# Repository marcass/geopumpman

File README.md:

# geopumpman
Manage climate in home using a geothermal heatpump, solvers, predictive weather models and PID control

## Components

### Software

* Predictor of thermal requirements
   * Weather data, eg https://pypi.org/project/weather-api/
* Observer of climate conditions, eg https://github.com/marcass/esp32-sensornet
   * Temperature sensors
      * In slab
      * In lower storey/upper storey
      * Outside
   * Lux sensors (light ingress)
* Controller of heating/cooling plant
   * PID control on heating/cooling demand
   * Solvers, eg https://github.com/Pyomo
   * Extended Kalman filter?
* Heating/cooling plant
   * Fail-safes
* UI (web?)

### Hardware
* Comission ground source heatpump
* containerise software for easier hardware transition 
* Standard brain running linux

# Links
* https://www.researchgate.net/publication/327136772_A_Python-Based_Toolbox_for_Model_Predictive_Control_Applied_to_Buildings
* https://filterpy.readthedocs.io/en/latest/kalman/ExtendedKalmanFilter.html

# Things to do
* Work out how to perist and share data between containers for influxdb

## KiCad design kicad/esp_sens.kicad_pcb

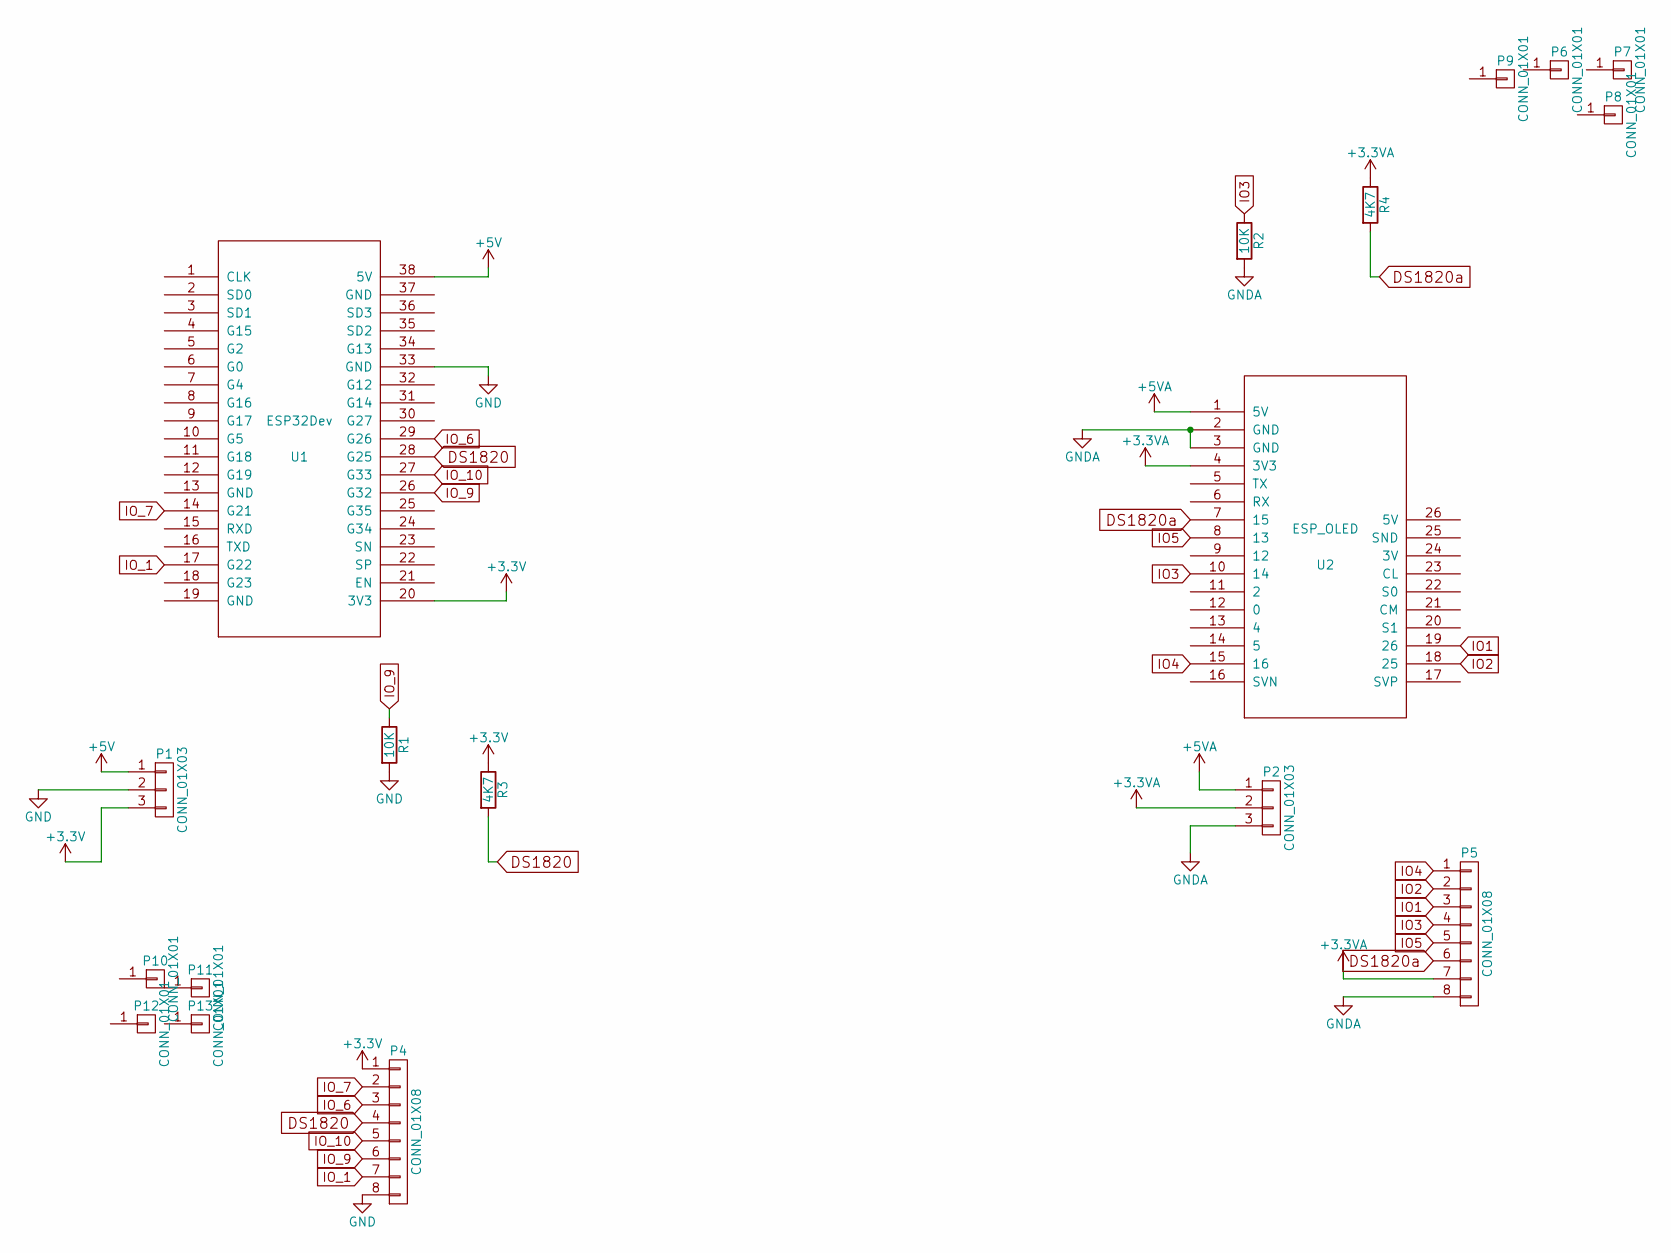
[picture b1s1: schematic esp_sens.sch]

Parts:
P1, P2: CONN_01X03; PhoenixContact_MCV_1,5_3-G-3.81_1x03_P3.81mm_Vertical
P4, P5: CONN_01X08; PhoenixContact_MCV_1,5_8-G-3.81_1x08_P3.81mm_Vertical
P6, P7, P8, P9, P10, P11, P12, P13: CONN_01X01; MountingHole_4.3mm_M4_DIN965_Pad
R1, R2: 10K; R_Axial_DIN0207_L6.3mm_D2.5mm_P10.16mm_Horizontal
R3, R4: 4K7; R_Axial_DIN0207_L6.3mm_D2.5mm_P10.16mm_Horizontal
U1: ESP32Dev; ESP32-DEV-WROOM
U2: ESP_OLED

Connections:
+3.3VA: P2.2, P5.7, R4.1, U2.4 (3V3)
+3V3: P1.3, P4.1, R3.1, U1.20 (3V3)
+5V: P1.1, U1.38 (5V)
+5VA: P2.1, U2.1 (5V)
DS1820: P4.4, R3.2, U1.28 (G25)
DS1820a: P5.6, R4.2, U2.7 (15)
GND: P1.2, P4.8, R1.2, U1.33 (GND)
GNDA: P2.3, P5.8, R2.2, U2.2 (GND), U2.3 (GND)
IO1: P5.3, U2.19 (26)
IO2: P5.2, U2.18 (25)
IO3: P5.4, R2.1, U2.10 (14)
IO4: P5.1, U2.15 (16)
IO5: P5.5, U2.8 (13)
IO_1: P4.7, U1.17 (G22)
IO_6: P4.3, U1.29 (G26)
IO_7: P4.2, U1.14 (G21)
IO_9: P4.6, R1.1, U1.26 (G32)
IO_10: P4.5, U1.27 (G33)

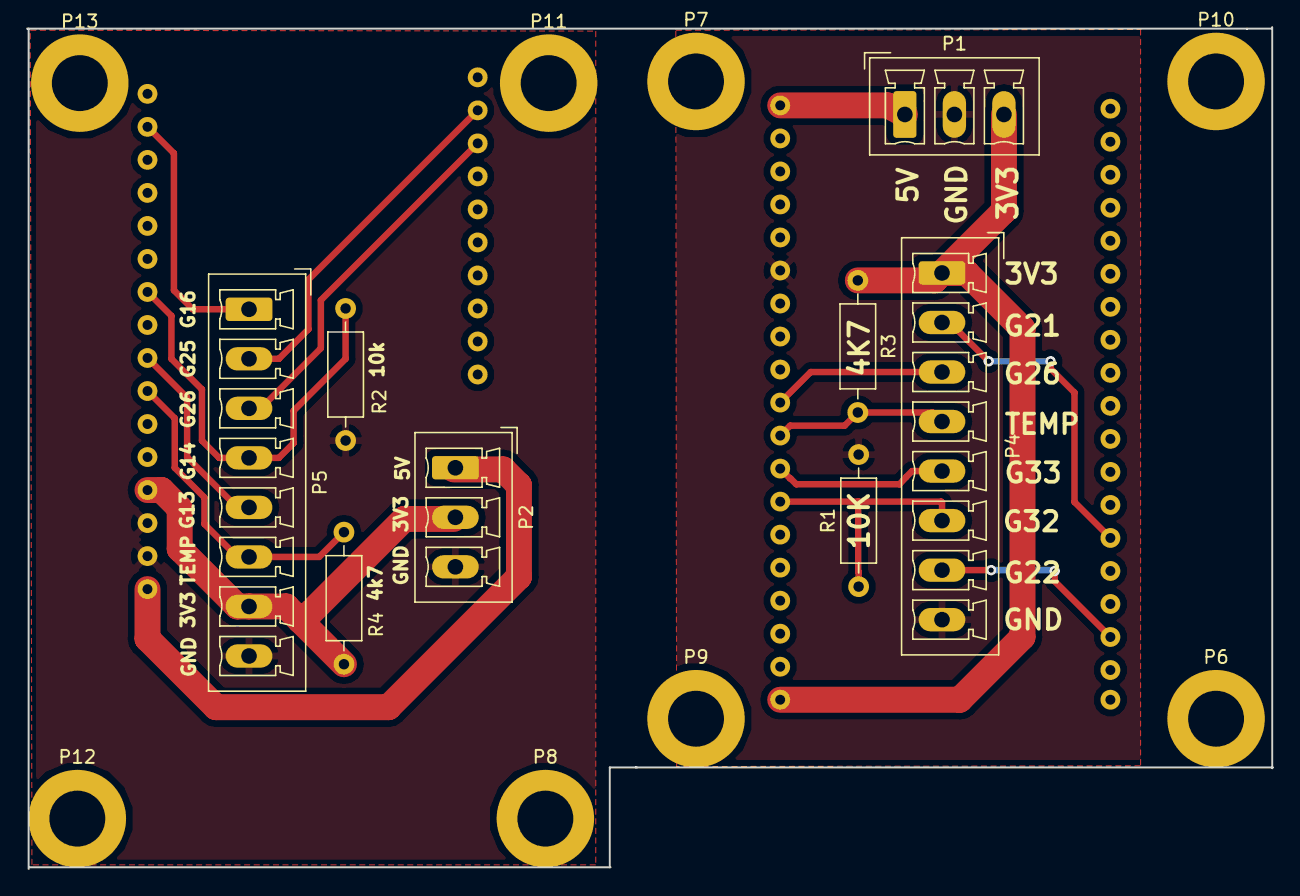
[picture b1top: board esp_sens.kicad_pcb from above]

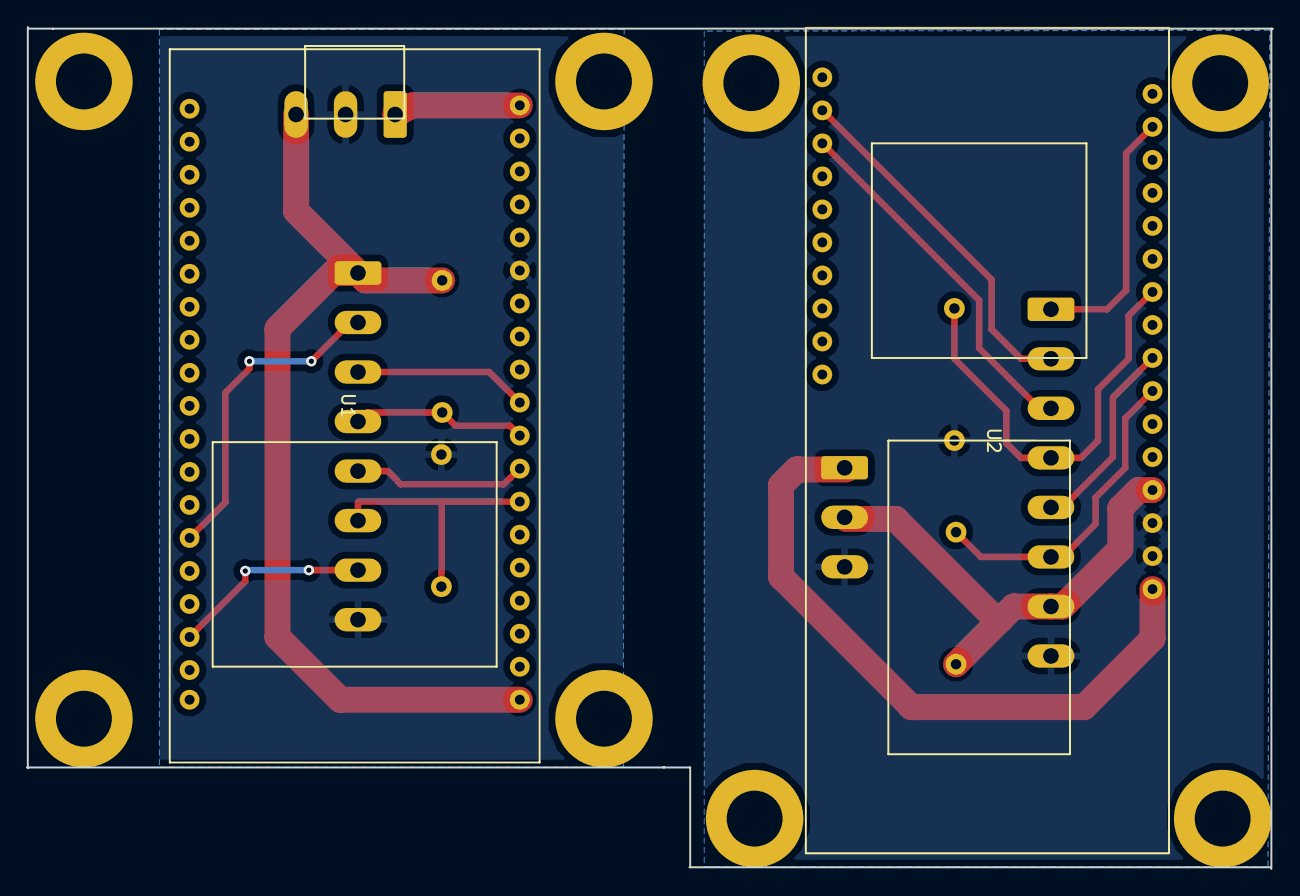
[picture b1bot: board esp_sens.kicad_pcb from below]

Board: 2 copper layers, 95.9 x 64.8 mm, 18 parts (2 on the bottom side), 18 nets.

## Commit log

2019-01-10 getting some structure and starting containerisation
2019-01-10 getting things arranged for testing sensors and peristent data in docker
2019-01-11 fiddling with weathe api
2019-01-14 using openweathermap
2019-01-15 can get sunny times
2019-04-12 started sensor platform
2019-04-12 2 boards in one
2019-04-12 pin reassignment...
2019-04-15 final board roundup
2019-04-15 label boards to do
2019-04-16 boards are labelled and plug size changed
2019-04-18 plotted boards
2019-10-09 started pcb for 1-wire connectors
2019-10-16 sketch for collecting temps
2019-10-16 added a serial listener
2019-10-16 timestamps...
2019-10-16 updated address
2019-10-17 sorting data
2019-10-17 working, just need to format timesstamp
2019-10-17 updated so datetime is now rendered as string
2019-10-17 sloed sampling rate
2019-10-17 added some data
2019-10-18 updated date separator
2019-10-18 adding plotting
2019-10-22 real world data
2019-11-03 started footprint for connector
2019-11-05 finsished model for rj45 connector
2019-11-06 soreted footprints
2019-11-06 started board
2019-11-07 added schottky diode
2019-11-08 laying out pcb
2019-11-15 finished pcd
2019-11-15 finished schematic
2019-12-04 new readings
2020-01-09 added ebugging
2020-01-13 added current temp data
2020-01-27 updated board for pcb enclosure
2020-01-28 board annotated
2020-01-29 board copied
2020-02-02 sent for production
2020-03-07 temps added
2020-03-26 more temps
2020-04-02 SVPWM added
2020-04-21 started getting some sine stuff sorted
2020-04-23 added more examples
2020-04-24 change duty cyclt and freq
2020-04-28 comp pwm
2020-04-28 comp pwm updated
2020-04-28 added dead time for comp pulses
2020-05-28 updated temps
2020-06-08 added data point
2020-08-14 sketch for pressure sensors
2020-08-21 added sucessful pressure test sketch
2020-08-21 fixed short cycling issue
2020-08-21 tidied up
